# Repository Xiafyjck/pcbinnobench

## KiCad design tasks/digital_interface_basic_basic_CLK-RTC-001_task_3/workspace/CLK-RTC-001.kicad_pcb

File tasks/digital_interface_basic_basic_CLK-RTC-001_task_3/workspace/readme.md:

# CLK-XTAL-001: MCU External High-Speed Crystal Board

STM32 minimum system board, connect high-speed crystal to it.

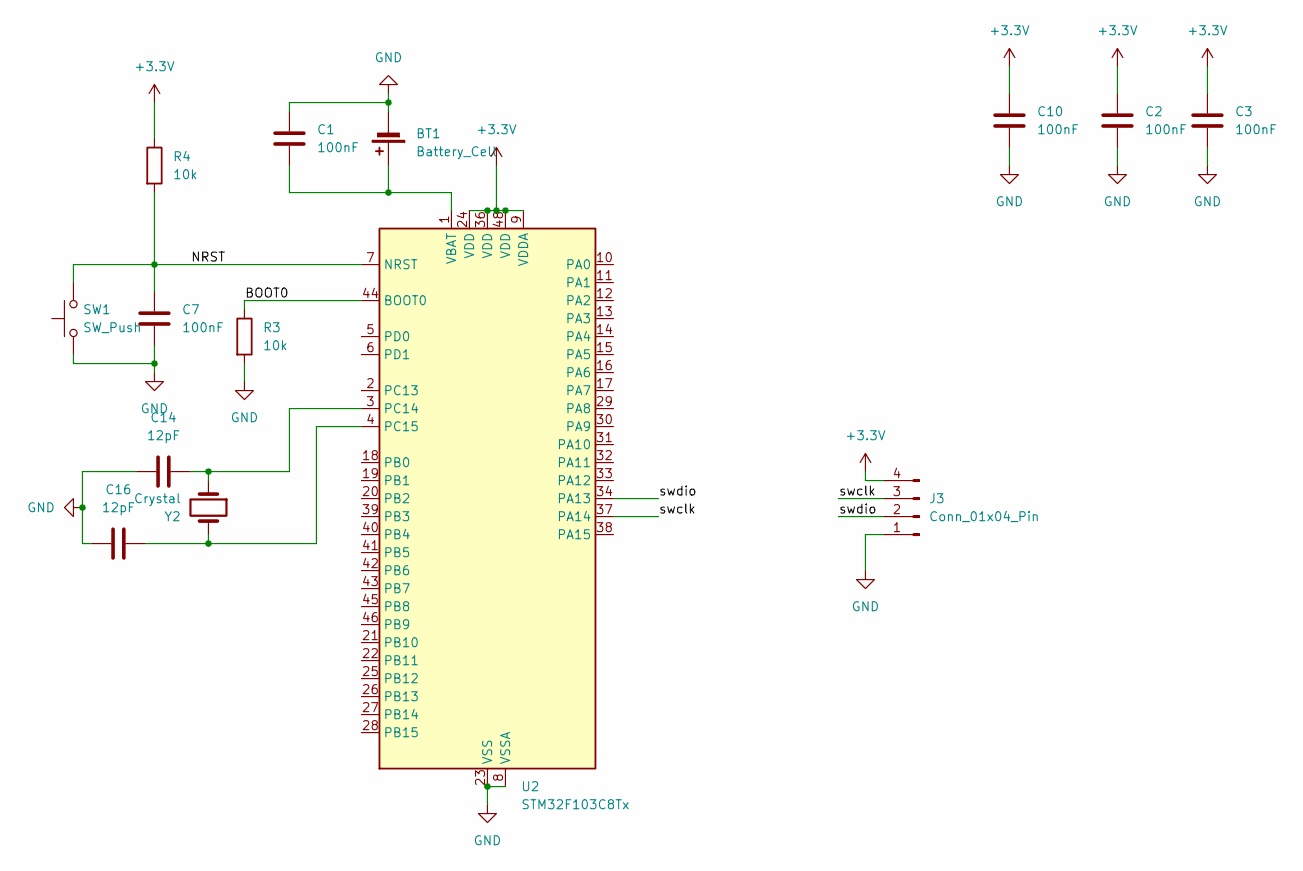
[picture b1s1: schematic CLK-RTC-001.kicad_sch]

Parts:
BT1: Battery_Cell; BatteryHolder_Keystone_500
C1, C2, C3, C7, C10: 100nF; C_0805_2012Metric
C14, C16: 12pF; C_0805_2012Metric
J3: Conn_01x04_Pin; JST_XH_B4B-XH-AM_1x04_P2.50mm_Vertical
R3, R4: 10k; R_0805_2012Metric
SW1: SW_Push; SW_PUSH_6mm
U2: STM32F103C8Tx; LQFP-48_7x7mm_P0.5mm
Y2: Crystal; Crystal_SMD_3215-2Pin_3.2x1.5mm

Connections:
+3.3V: C2.1, C3.1, C10.1, J3.4, R4.1, U2.9 (VDDA), U2.24 (VDD), U2.36 (VDD), U2.48 (VDD)
/BOOT0: R3.1, U2.44 (BOOT0)
/NRST: C7.1, R4.2, SW1.2, U2.7 (NRST)
/swclk: J3.3, U2.37 (PA14)
/swdio: J3.2, U2.34 (PA13)
GND: BT1.2 (-), C1.1, C2.2, C3.2, C7.2, C10.2, C14.1, C16.1, J3.1, R3.2, SW1.1, U2.8 (VSSA), U2.23 (VSS), U2.35 (VSS), U2.47 (VSS)
unnamed: BT1.1 (+), C1.2, U2.1 (VBAT)
unnamed: C14.2, U2.3 (PC14), Y2.1
unnamed: C16.2, U2.4 (PC15), Y2.2

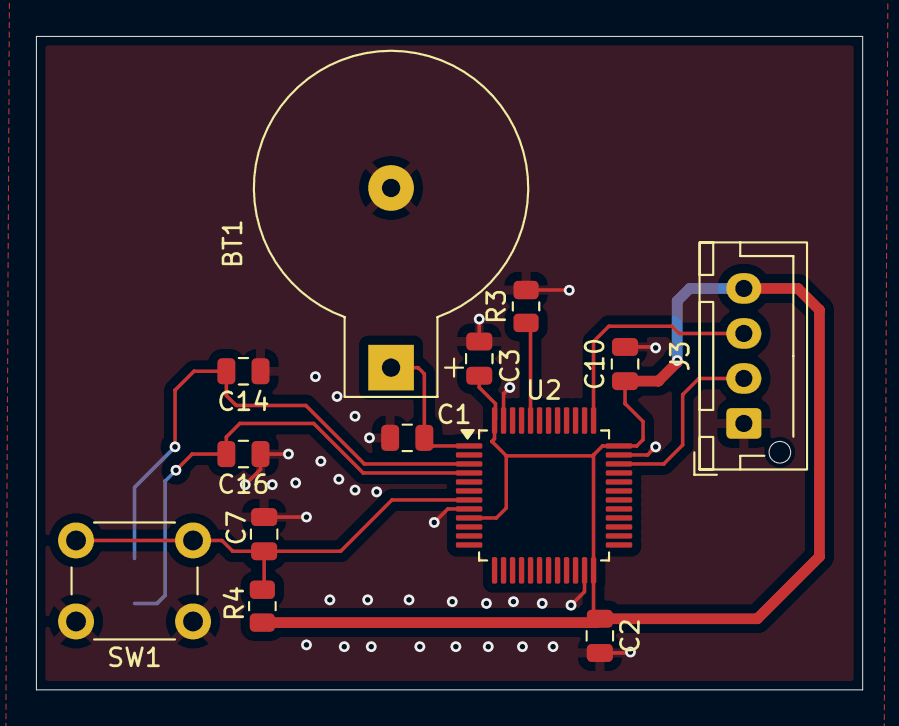
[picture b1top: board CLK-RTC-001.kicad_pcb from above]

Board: 2 copper layers, 45.9 x 36.3 mm, 14 parts (1 on the bottom side), 9 nets.

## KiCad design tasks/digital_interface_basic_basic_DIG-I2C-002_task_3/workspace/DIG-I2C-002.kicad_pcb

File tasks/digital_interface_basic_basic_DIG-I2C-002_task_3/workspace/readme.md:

This project aims to connect MCU with SHT30 and LM75B for communication.
Schematic part:
Each power supply pin of the MCU has a decoupling capacitor.
NRST pin pulled high.
BOOT0 pin pulled low.
PB10 as I2C SCL pin, PB11 as SDA pin.
PB12, PB13 as general-purpose MCU pins.
I2C SCL and SDA pulled high.
SHT30 R pin connected to GND, RESET pulled high, ADDR pin pulled low.
LM75B A0, A1, A2 address pins pulled low.
PCB part:
Decoupling capacitors placed near power pins.

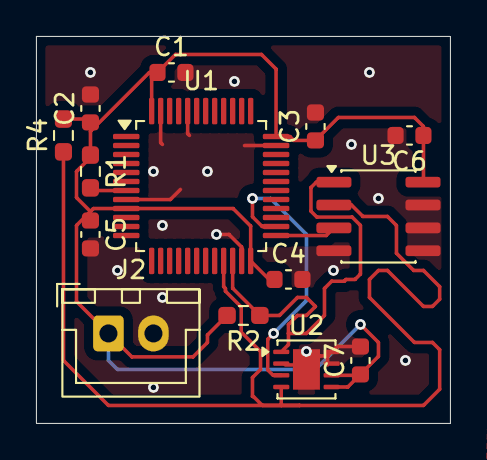
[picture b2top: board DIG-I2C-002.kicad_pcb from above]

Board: 2 copper layers, 23.0 x 21.5 mm, 14 parts (0 on the bottom side), 7 nets.

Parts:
C1, C2, C3, C4, C5, C6, C7: 100NF; C_0603_1608Metric
J2: Conn_01x02_Pin; JST_XH_B2B-XH-A_1x02_P2.50mm_Vertical
R1: 10K; R_0603_1608Metric_Pad0.98x0.95mm_HandSolder
R2, R4: 4.7K; R_0603_1608Metric_Pad0.98x0.95mm_HandSolder
U1: STM32F103C8Tx; LQFP-48_7x7mm_P0.5mm
U2: SHT30-DIS; DFN-8-1EP_3x3mm_P0.65mm_EP1.5x2.25mm
U3: LM75B; SOIC-8_3.9x4.9mm_P1.27mm

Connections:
+3V3: C1.1, C2.1, C3.1, C4.1, C5.1, C6.1, C7.1, J2.1, R1.1, R2.2, R4.2, U1.9 (VDDA), U1.24 (VDD), U1.36 (VDD), U1.48 (VDD), U2.5 (VDD), U2.6 (~RESET), U3.8 (+Vs)
/groundtruth1/ALERT: U1.26 (PB13), U2.3 (ALERT)
/groundtruth1/I2C_SCL: R4.1, U1.21 (PB10), U2.4 (SCL), U3.2 (SCL)
/groundtruth1/I2C_SDA: R2.1, U1.22 (PB11), U2.1 (SDA), U3.1 (SDA)
/groundtruth1/O.S: U1.25 (PB12), U3.3 (O.S.)
GND: C1.2, C2.2, C3.2, C4.2, C5.2, C6.2, C7.2, J2.2, U1.8 (VSSA), U1.23 (VSS), U1.35 (VSS), U1.44 (BOOT0), U1.47 (VSS), U2.2 (ADDR), U2.7 (R), U2.8 (VSS), U2.9 (VSS), U3.4 (GND), U3.5 (A2), U3.6 (A1), U3.7 (A0)
unnamed: R1.2, U1.7 (NRST)

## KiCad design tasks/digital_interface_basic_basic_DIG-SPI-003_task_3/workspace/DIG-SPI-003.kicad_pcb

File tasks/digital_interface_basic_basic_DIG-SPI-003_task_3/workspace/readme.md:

This system uses STM32 MCU to connect two SPI Flash devices W25Q32 and W25Q128 via shared SPI bus (SCK, MOSI, MISO). Each Flash has its own chip select CS pin; device switching is achieved by pulling different CS low in time division. The deselected Flash sets its MISO pin to high impedance to avoid bus signal conflicts. Both Flash support the same SPI modes 0/3 and are powered by 3.3V, so no level shifting is needed. In PCB layout, the SPI bus adopts a star topology centered on the master device, with branches as equal length as possible and close to the corresponding Flash to ensure signal integrity.

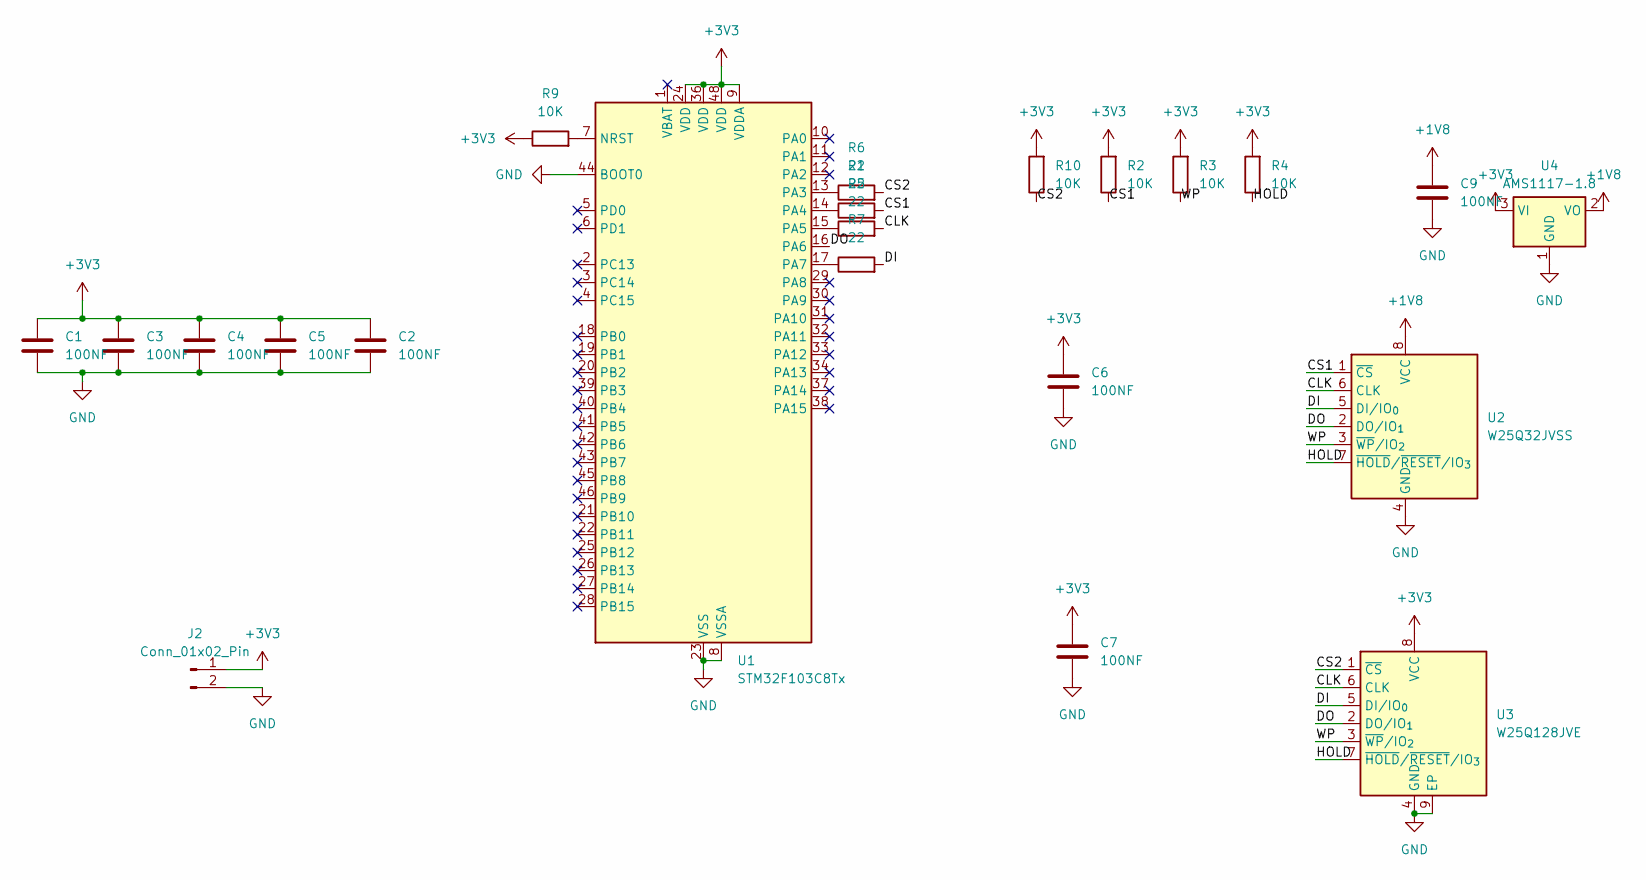
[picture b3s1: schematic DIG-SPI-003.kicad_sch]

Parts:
C1, C2, C3, C4, C5, C6, C7, C9: 100NF; C_0603_1608Metric
J2: Conn_01x02_Pin; JST_XH_B2B-XH-A_1x02_P2.50mm_Vertical
R1, R5, R6, R7: 22; R_0201_0603Metric
R2, R3, R4, R9, R10: 10K; R_0603_1608Metric
U1: STM32F103C8Tx; LQFP-48_7x7mm_P0.5mm
U2: W25Q32JVSS; SOIC-8_5.3x5.3mm_P1.27mm
U3: W25Q128JVE; WSON-8-1EP_6x5mm_P1.27mm_EP3.4x4.3mm
U4: AMS1117-1.8; SOT-223-3_TabPin2

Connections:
+1V8: C9.1, U2.8 (VCC), U4.2 (VO)
+3V3: C1.1, C2.1, C3.1, C4.1, C5.1, C6.1, C7.1, J2.1, R2.2, R3.2, R4.2, R9.1, R10.2, U1.9 (VDDA), U1.24 (VDD), U1.36 (VDD), U1.48 (VDD), U3.8 (VCC), U4.3 (VI)
/CLK: R5.2, U2.6 (CLK), U3.6 (CLK)
/CS1: R1.2, R2.1, U2.1 (~CS)
/CS2: R6.2, R10.1, U3.1 (~CS)
/DI: R7.2, U2.5 (DI/IO_{0}), U3.5 (DI/IO_{0})
/DO: U1.16 (PA6), U2.2 (DO/IO_{1}), U3.2 (DO/IO_{1})
/HOLD: R4.1, U2.7 (~HOLD/~RESET/IO_{3}), U3.7 (~HOLD/~RESET/IO_{3})
/WP: R3.1, U2.3 (~WP/IO_{2}), U3.3 (~WP/IO_{2})
GND: C1.2, C2.2, C3.2, C4.2, C5.2, C6.2, C7.2, C9.2, J2.2, U1.8 (VSSA), U1.23 (VSS), U1.35 (VSS), U1.44 (BOOT0), U1.47 (VSS), U2.4 (GND), U3.4 (GND), U3.9 (EP), U4.1 (GND)
unnamed: R9.2, U1.7 (NRST)
unnamed: R6.1, U1.13 (PA3)
unnamed: R1.1, U1.14 (PA4)
unnamed: R5.1, U1.15 (PA5)
unnamed: R7.1, U1.17 (PA7)

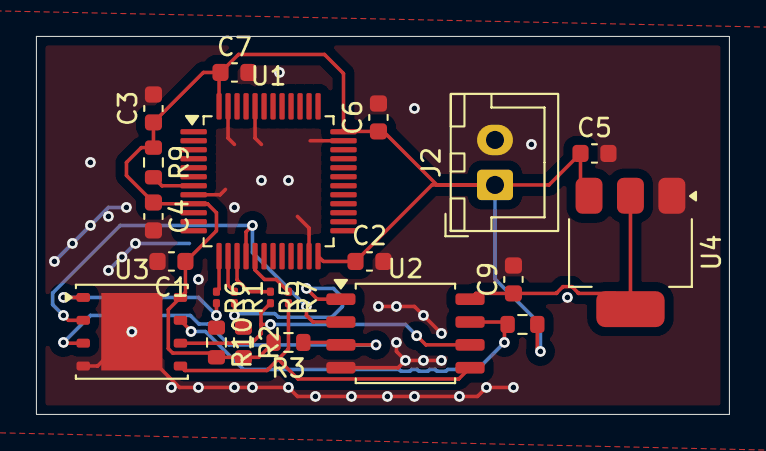
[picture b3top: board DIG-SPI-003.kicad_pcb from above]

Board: 2 copper layers, 38.5 x 21.0 mm, 22 parts (0 on the bottom side), 15 nets.

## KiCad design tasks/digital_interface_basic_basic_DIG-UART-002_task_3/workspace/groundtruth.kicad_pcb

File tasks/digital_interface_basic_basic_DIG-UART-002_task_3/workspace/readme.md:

This project aims to connect MCU UART via USB-to-serial chip, using CH340C. USB D+/D- signals are connected to CH340C through necessary series resistors; since they are differential signals, differential routing is required. For ESD protection, SRV05-4 is added. On the UART side, TX, RX, GND, and 3.3V are connected to MCU, with signals brought out via pin headers. Series resistors of 22-100 ohms are added between TX and RX. Also, to prevent current surge during programming, a 10uF local storage capacitor is placed close to CH340.

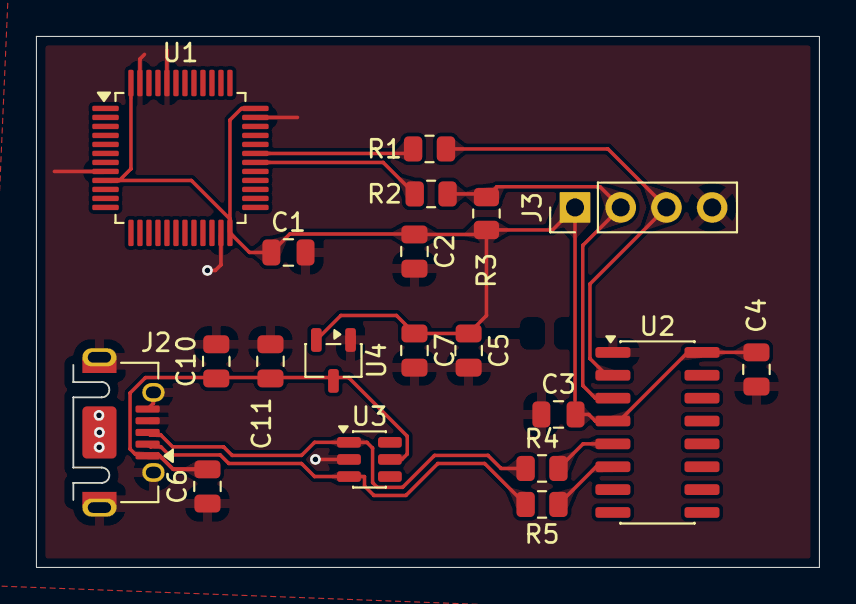
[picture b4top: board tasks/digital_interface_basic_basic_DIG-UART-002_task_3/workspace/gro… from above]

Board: 2 copper layers, 43.5 x 29.5 mm, 20 parts (0 on the bottom side), 11 nets.

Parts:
C1: 0.1uf; C_0805_2012Metric
C2: 1uf; C_0805_2012Metric
C3, C4, C7, C11: 100nf; C_0805_2012Metric
C5, C6, C10: 10uf; C_0805_2012Metric
J2: USB_B_Micro; USB_Micro-AB_Molex_47590-0001
J3: Conn_01x04_Pin; PinHeader_1x04_P2.54mm_Vertical
R1, R2: 50; R_0805_2012Metric
R3: 10k; R_0805_2012Metric
R4, R5: 22; R_0805_2012Metric
U1: STM32F103C8Tx; LQFP-48_7x7mm_P0.5mm
U2: CH340C; SOIC-16_3.9x9.9mm_P1.27mm
U3: SRV05-4; SOT-23-6
U4: XC6206PxxxMR; SOT-23-3

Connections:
+3V3: C1.1, C2.1, C3.2, C4.2, C5.1, C7.1, J3.1, R3.2, U1.9 (VDDA), U1.24 (VDD), U1.36 (VDD), U1.48 (VDD), U2.4 (V3), U2.16 (VCC), U4.2 (VO)
+5V: C6.2, C10.1, C11.1, J2.1 (VBUS), U3.5 (VP), U4.3 (VI)
/usb-uart/D+: J2.3 (D+), R4.1, U3.1 (IO1)
/usb-uart/D-: J2.2 (D-), R5.2, U3.3 (IO2)
/usb-uart/RX: J3.2, R2.2, R3.1, U2.3 (RXD)
/usb-uart/TX: J3.3, R1.2, U2.2 (TXD)
GND: C1.2, C2.2, C3.1, C4.1, C5.2, C6.1, C7.2, C10.2, C11.2, J2.4 (ID), J2.5 (GND), J2.6 (Shield), J3.4, U1.8 (VSSA), U1.23 (VSS), U1.35 (VSS), U1.44 (BOOT0), U1.47 (VSS), U2.1 (GND), U3.2 (VN), U4.1 (GND)
unnamed: R2.1, U1.30 (PA9)
unnamed: R1.1, U1.31 (PA10)
unnamed: R4.2, U2.5 (UD+)
unnamed: R5.1, U2.6 (UD-)

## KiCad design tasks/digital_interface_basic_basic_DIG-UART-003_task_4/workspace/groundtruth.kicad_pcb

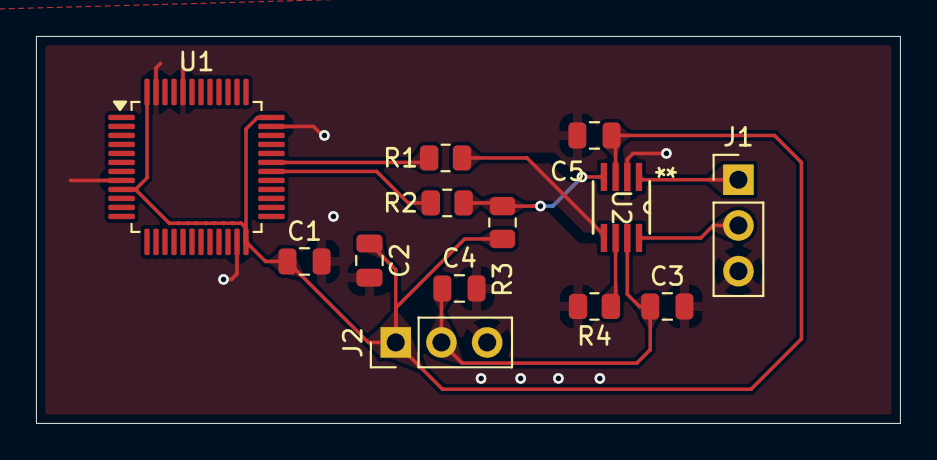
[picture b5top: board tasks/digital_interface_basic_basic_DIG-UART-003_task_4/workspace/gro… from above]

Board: 2 copper layers, 48.0 x 21.5 mm, 13 parts (0 on the bottom side), 10 nets.

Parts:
C1, C3, C4, C5: 0.1uf; C_0805_2012Metric
C2: 1uf; C_0805_2012Metric
J1, J2: Conn_01x03_Pin; PinHeader_1x03_P2.54mm_Vertical
R1, R2: 50; R_0805_2012Metric
R3, R4: 10k; R_0805_2012Metric
U1: STM32F103C8Tx; LQFP-48_7x7mm_P0.5mm
U2: TXS0102DCTR; DCT8

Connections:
+3V3: C1.1, C2.1, C5.1, J2.1, R3.2, U1.9 (VDDA), U1.24 (VDD), U1.36 (VDD), U1.48 (VDD), U2.3 (VCCA)
+5V: C3.1, C4.1, J2.2, U2.7 (VCCB)
/stm32-uart/RX: R1.2, U2.5 (A1)
/stm32-uart/TX: R2.2, R3.1, U2.4 (A2)
/usb-uart/RX_5V: J1.1, U2.1 (B2)
/usb-uart/TX_5V: J1.2, U2.8 (B1)
GND: C1.2, C2.2, C3.2, C4.2, C5.2, J1.3, J2.3, R4.2, U1.8 (VSSA), U1.23 (VSS), U1.35 (VSS), U1.44 (BOOT0), U1.47 (VSS), U2.2 (GND)
unnamed: R2.1, U1.30 (PA9)
unnamed: R1.1, U1.31 (PA10)
unnamed: R4.1, U2.6 (OE)

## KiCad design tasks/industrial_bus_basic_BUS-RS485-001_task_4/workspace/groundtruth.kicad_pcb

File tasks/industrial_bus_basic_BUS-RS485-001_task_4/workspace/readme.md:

This project implements failsafe idle biasing for RS485 bus. It uses SP3485 as RS485 transceiver, with DE signal controlling both DE and RE# to switch between transmit/receive direction. B line is pulled up to VCC via 10kΩ resistor, A line is pulled down to GND via 10kΩ resistor, implementing external failsafe idle biasing. A 120Ω termination resistor is reserved between A and B, default NC, soldered only when this node is at the physical end of the bus.

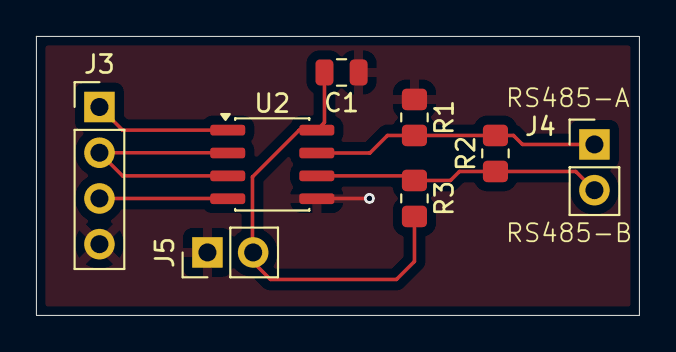
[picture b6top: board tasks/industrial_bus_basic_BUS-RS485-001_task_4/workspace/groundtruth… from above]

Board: 2 copper layers, 33.5 x 15.5 mm, 8 parts (0 on the bottom side), 7 nets.

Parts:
C1: 2.2uf; C_0805_2012Metric
J3: Conn_01x04_Pin; PinHeader_1x04_P2.54mm_Vertical
J4, J5: Conn_01x02_Pin; PinHeader_1x02_P2.54mm_Vertical
R1, R3: 10K; R_0805_2012Metric_Pad1.20x1.40mm_HandSolder
R2: 120; R_0805_2012Metric_Pad1.20x1.40mm_HandSolder
U2: SP3485EN; SOIC-8_3.9x4.9mm_P1.27mm

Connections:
+3V3: C1.2, J5.2, R3.2, U2.8 (VCC)
/RS485_2A: J4.2, R2.1, R3.1, U2.6 (A)
/RS485_2B: J4.1, R1.2, R2.2, U2.7 (B)
/RS485_2_DE: J3.2, U2.2 (~RE), U2.3 (DE)
/RS485_2_RX: J3.1, U2.1 (RO)
/RS485_2_TX: J3.3, U2.4 (DI)
GND: C1.1, J3.4, J5.1, R1.1, U2.5 (GND)

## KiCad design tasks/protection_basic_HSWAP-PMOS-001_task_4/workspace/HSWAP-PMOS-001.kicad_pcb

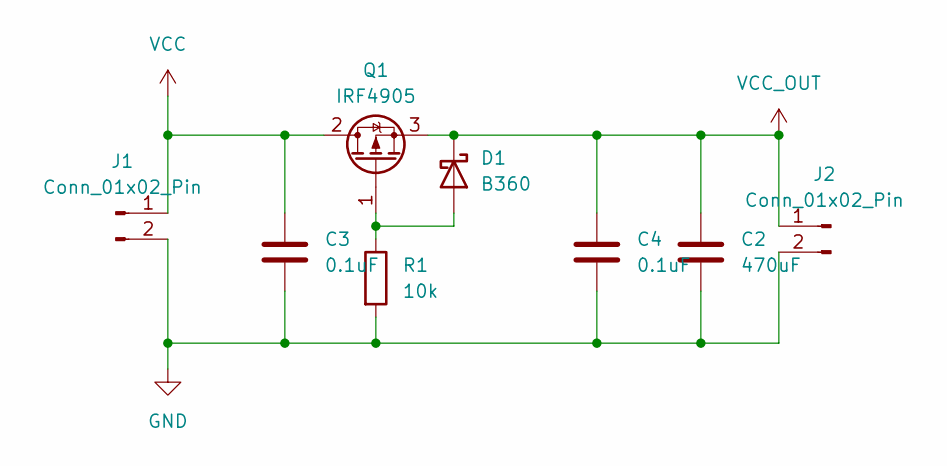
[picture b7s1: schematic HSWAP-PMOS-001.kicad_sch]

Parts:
C2: 470uF; C_Disc_D7.5mm_W5.0mm_P10.00mm
C3, C4: 0.1uF; C_0805_2012Metric
D1: B360; D_SMC
J1, J2: Conn_01x02_Pin; JST_NV_B02P-NV_1x02_P5.00mm_Vertical
Q1: IRF4905; TO-220-3_Vertical
R1: 10k; R_0805_2012Metric

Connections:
GND: C2.2, C3.2, C4.2, J1.2, J2.2, R1.2
unnamed: D1.2 (A), Q1.1 (G), R1.1
VCC: C3.1, J1.1, Q1.2 (D)
VCC_OUT: C2.1, C4.1, D1.1 (K), J2.1, Q1.3 (S)

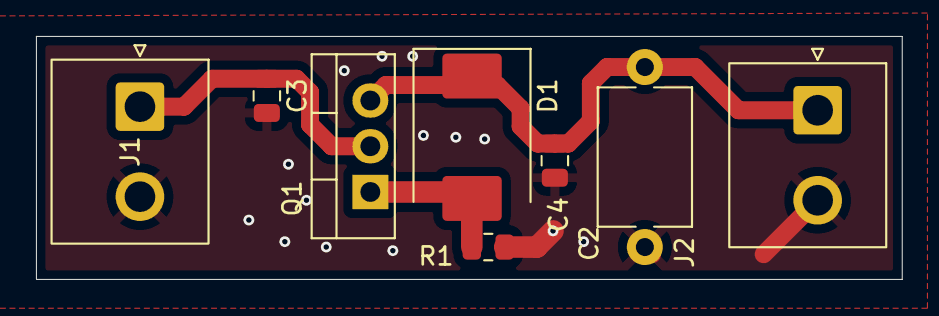
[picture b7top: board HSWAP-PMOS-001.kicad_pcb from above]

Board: 2 copper layers, 48.1 x 13.5 mm, 8 parts (0 on the bottom side), 4 nets.

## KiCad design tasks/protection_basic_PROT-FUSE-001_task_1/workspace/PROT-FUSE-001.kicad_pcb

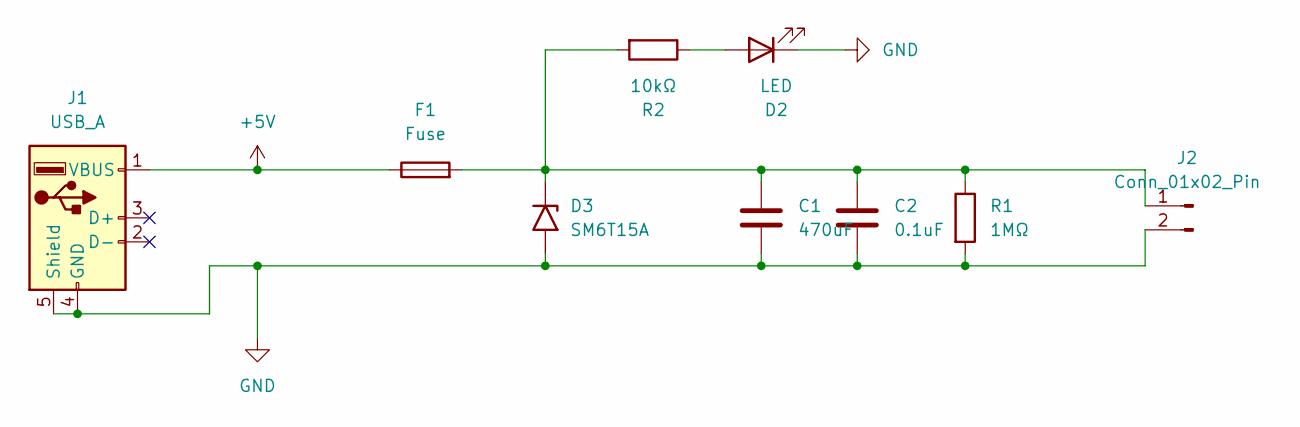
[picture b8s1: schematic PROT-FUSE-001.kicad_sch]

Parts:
C1: 470uF; C_Disc_D9.0mm_W5.0mm_P10.00mm
C2: 0.1uF; C_0805_2012Metric
D2: LED; LED_0805_2012Metric
D3: SM6T15A; D_SMB
F1: Fuse; L_0402_1005Metric
J1: USB_A; USB_A_TE_292303-7_Horizontal
J2: Conn_01x02_Pin; JST_EH_B2B-EH-A_1x02_P2.50mm_Vertical
R1: 1MΩ; R_0805_2012Metric
R2: 10kΩ; R_0805_2012Metric

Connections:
+5V: F1.1, J1.1 (VBUS)
GND: C1.2, C2.2, D2.1 (K), D3.2 (A2), J1.4 (GND), J1.5 (Shield), J2.2, R1.2
unnamed: D2.2 (A), R2.1
unnamed: C1.1, C2.1, D3.1 (A1), F1.2, J2.1, R1.1, R2.2

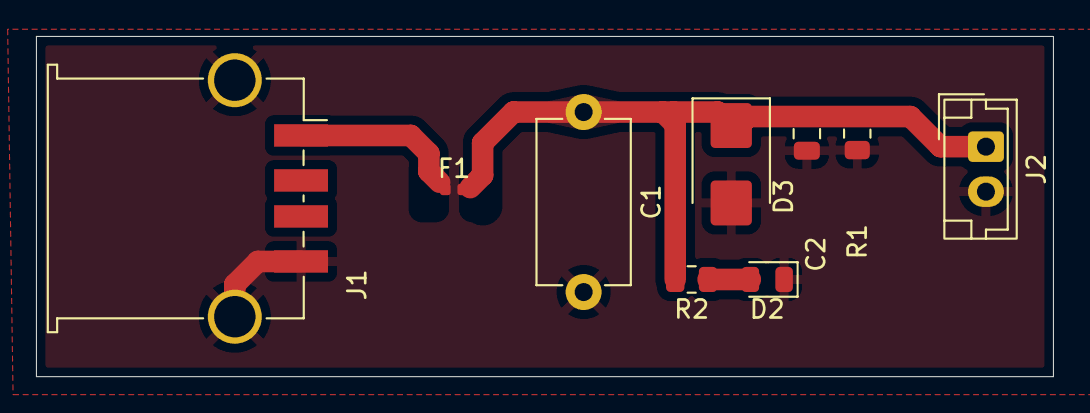
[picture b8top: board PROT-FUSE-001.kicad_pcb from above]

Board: 2 copper layers, 56.5 x 18.9 mm, 9 parts (0 on the bottom side), 4 nets.
